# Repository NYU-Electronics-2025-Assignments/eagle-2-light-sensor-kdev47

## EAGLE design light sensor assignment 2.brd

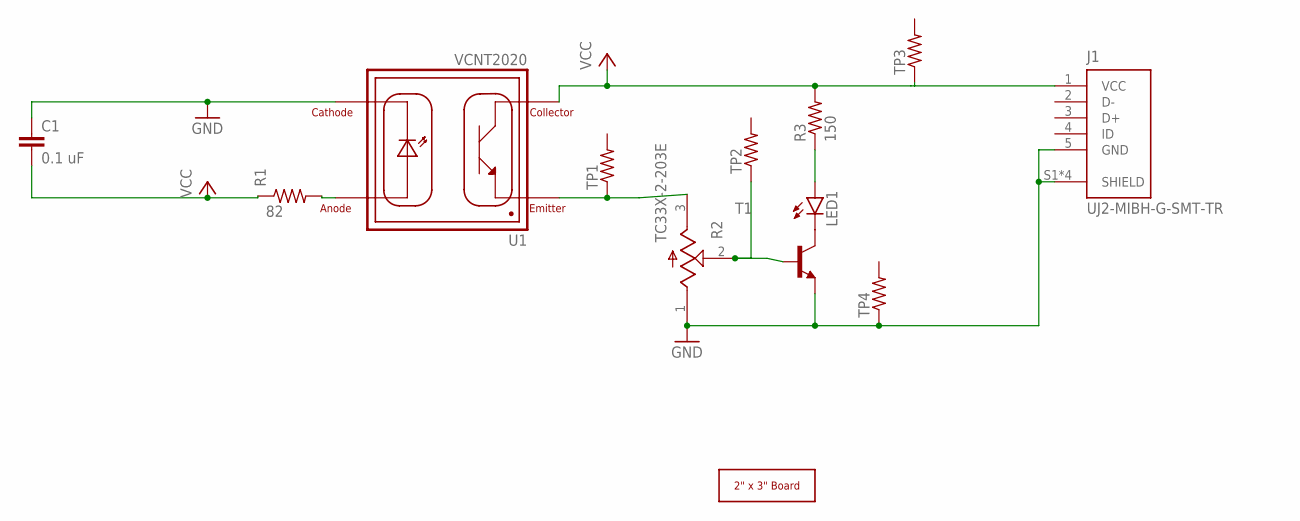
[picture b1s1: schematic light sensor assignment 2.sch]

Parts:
C1: 0.1 uF; C1206
J1: UJ2-MIBH-G-SMT-TR; CUI_UJ2-MIBH-G-SMT-TR
LED1: LEDSML0805; SML0805
R1: 82; R0805
R2: TC33X-2-203E; TRIM_TC33X-2-203E
R3: 150; R0805
T1: -NPN-SOT23-EBC; SOT23-EBC
TP1, TP2, TP3, TP4: R-US_R1206; R1206
U1: VCNT2020; XDCR_VCNT2020
U$1: 2X3_BOARD_V2

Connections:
GND: J1.5 (GND), J1.S1 (SHIELD), J1.S2 (SHIELD), J1.S3 (SHIELD), J1.S4 (SHIELD), R2.1 (CCW), T1.E, TP4.1
unnamed: R1.2, U1.3 (ANODE)
unnamed: C1.1, U1.4 (CATHODE)
unnamed: R2.3 (CW), TP1.1, U1.1 (EMITTER)
unnamed: R2.2 (W), T1.B, TP2.1
unnamed: LED1.C, T1.C
unnamed: LED1.A, R3.1
VCC: C1.2, J1.1 (VCC), R1.1, R3.2, TP3.1, U1.2 (COLLECTOR)

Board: 2 copper layers, 13 parts (0 on the bottom side), 8 nets, no tracks yet.

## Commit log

2025-04-14 Light sensor
